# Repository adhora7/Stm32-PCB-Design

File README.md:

# Stm32 PCB Design

This repository contains the complete KiCad project files, Gerber files, and documentation for a two-layer PCB designed around the STM32F103C8T6 microcontroller.

---

## Project Overview

- **Microcontroller:** STM32F103C8T6
- **Software Used:** KiCad (version XX.X)
- **Layers:** 2-layer PCB (Top and Bottom)
- **USB Connector:** Micro USB for power and communication
- **Features:**
  - Crystal oscillator circuit for clock
  - Reset switch and reset circuitry
  - Voltage regulator (AMS1117 3.3V)
  - Decoupling capacitors for stable operation
  - USB interface pins for programming and communication
  - Mounting holes for secure fitting

---

## Repository Contents

- `KiCad_Files/` — Schematic and PCB design files for KiCad
- `Gerber_Files/` — Exported Gerber files ready for manufacturing

- `3D_Models/` — 3D renderings and images of the PCB layout
- `Documentation/` — Additional notes, and references

---

## How to Use

1. Open the schematic (`schematic.sch`) and PCB layout (`pcb.kicad_pcb`) files in KiCad.
2. Review the design, and if needed, modify according to your project requirements.
3. Use the Gerber files in the `Gerber_Files` folder to send to a PCB manufacturer.
4. Use the 3D models for visual verification and mechanical fitting.

---

## Design Considerations

- The power supply circuit uses AMS1117 to convert USB 5V to 3.3V needed by the STM32.
- USB signals are routed carefully to minimize noise.
- Decoupling capacitors are placed near the MCU pins for stable voltage.
- The board outline and mounting holes are designed for standard enclosures.

---

## Contact

For questions or collaboration, please reach out at fariaanowara82@gmail.com

---

## Screenshots / Images

*3D rendering of the STM32 PCB showing component placement and routing on the two-layer board.*
---

*This project is ideal for embedded system developers who want a ready-to-use STM32 PCB design with USB interface and basic power management.*

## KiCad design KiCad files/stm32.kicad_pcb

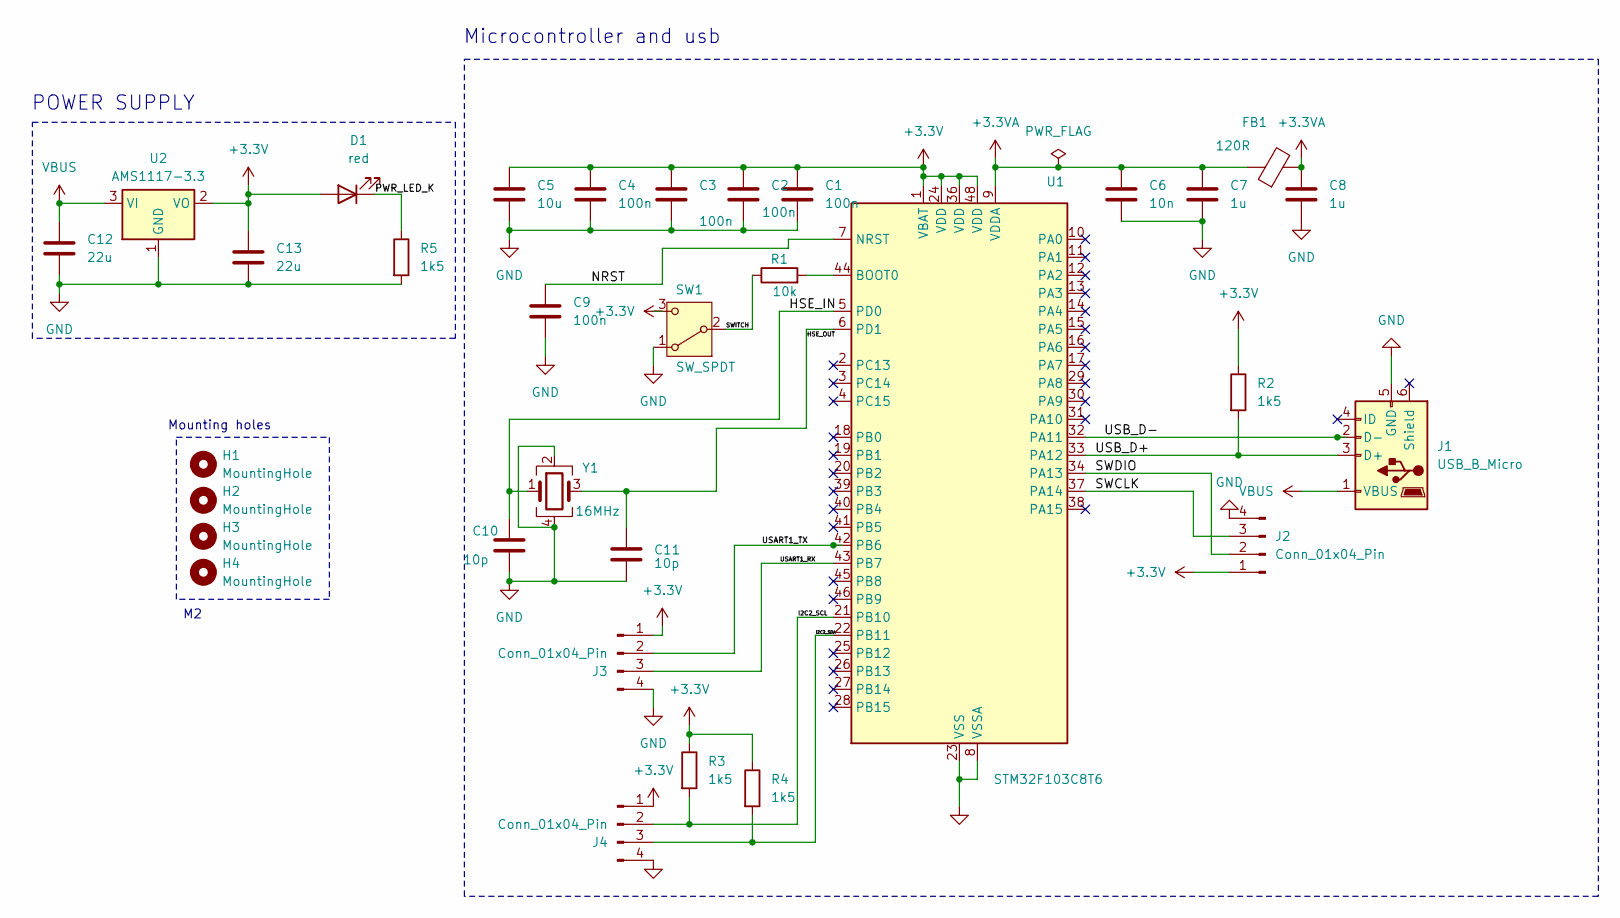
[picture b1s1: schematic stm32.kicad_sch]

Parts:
C1, C2, C3, C4, C9: 100n; C_0402_1005Metric
C5: 10u; C_0603_1608Metric
C6: 10n; C_0402_1005Metric
C7, C8: 1u; C_0402_1005Metric
C10, C11: 10p; C_0402_1005Metric
C12, C13: 22u; C_0805_2012Metric
D1: red; LED_0603_1608Metric
FB1: 120R; L_0603_1608Metric
H1, H2, H3, H4: MountingHole; MountingHole_2.2mm_M2
J1: USB_B_Micro; USB_Micro-B_Wuerth_629105150521
J2, J3, J4: Conn_01x04_Pin; PinHeader_1x04_P2.54mm_Vertical
R1: 10k; R_0402_1005Metric
R2, R3, R4, R5: 1k5; R_0402_1005Metric
SW1: SW_SPDT; SW_SPDT_PCM12
U1: STM32F103C8T6; LQFP-48_7x7mm_P0.5mm
U2: AMS1117-3.3; SOT-223-3_TabPin2
Y1: 16MHz; Crystal_SMD_3225-4Pin_3.2x2.5mm

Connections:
+3.3V: C1.1, C2.1, C3.1, C4.1, C5.1, C13.1, D1.2 (A), J2.1, J3.1, J4.1, R2.1, R3.1, R4.1, SW1.3 (C), U1.1 (VBAT), U1.24 (VDD), U1.36 (VDD), U1.48 (VDD), U2.2 (VO)
+3.3VA: C6.1, C7.1, C8.1, FB1.1, FB1.2, U1.9 (VDDA)
/HSE_IN: C10.1, U1.5 (PD0), Y1.1
/HSE_OUT: C11.1, U1.6 (PD1), Y1.3
/I2C2_SCL: J4.2, R3.2, U1.21 (PB10)
/I2C2_SDA: J4.3, R4.2, U1.22 (PB11)
/NRST: C9.1, U1.7 (NRST)
/PWR_LED_K: D1.1 (K), R5.1
/SWCLK: J2.3, U1.37 (PA14)
/SWDIO: J2.2, U1.34 (PA13)
/SWITCH: R1.1, SW1.2 (B)
/USART1_RX: J3.3, U1.43 (PB7)
/USART1_TX: J3.2, U1.42 (PB6)
/USB_D+: J1.3 (D+), R2.2, U1.33 (PA12)
/USB_D-: J1.2 (D-), U1.32 (PA11)
GND: C1.2, C2.2, C3.2, C4.2, C5.2, C6.2, C7.2, C8.2, C9.2, C10.2, C11.2, C12.2, C13.2, J1.5 (GND), J2.4, J3.4, J4.4, R5.2, SW1.1 (A), U1.8 (VSSA), U1.23 (VSS), U1.35 (VSS), U1.47 (VSS), U2.1 (GND), Y1.2, Y1.4
unnamed: R1.2, U1.44 (BOOT0)
VBUS: C12.1, J1.1 (VBUS), U2.3 (VI)

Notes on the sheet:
Mounting holes
Microcontroller and usb
POWER SUPPLY

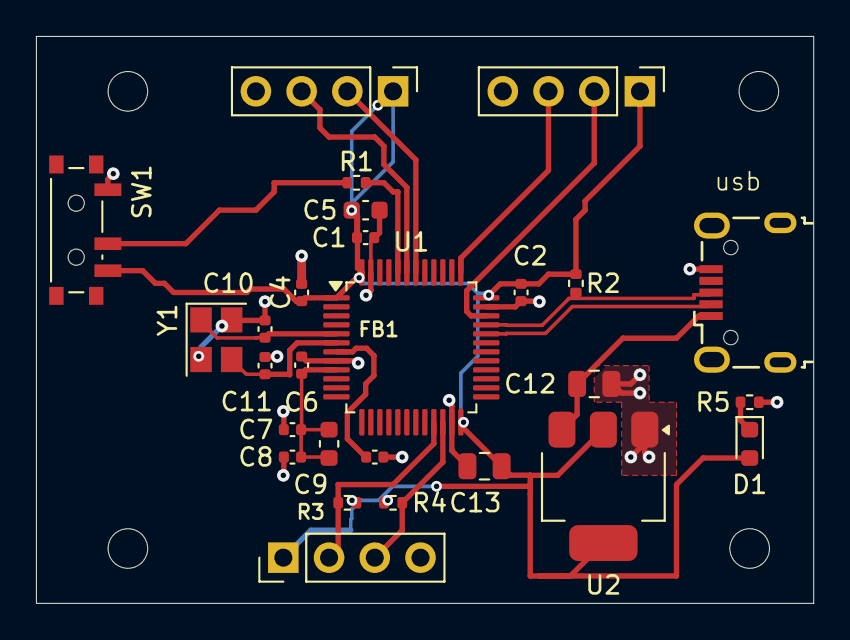
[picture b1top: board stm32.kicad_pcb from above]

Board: 2 copper layers, 43.2 x 31.5 mm, 31 parts (0 on the bottom side), 18 nets.

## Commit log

2025-05-16 added some files
2025-05-16 deleted some files
2025-05-16 done some changes
